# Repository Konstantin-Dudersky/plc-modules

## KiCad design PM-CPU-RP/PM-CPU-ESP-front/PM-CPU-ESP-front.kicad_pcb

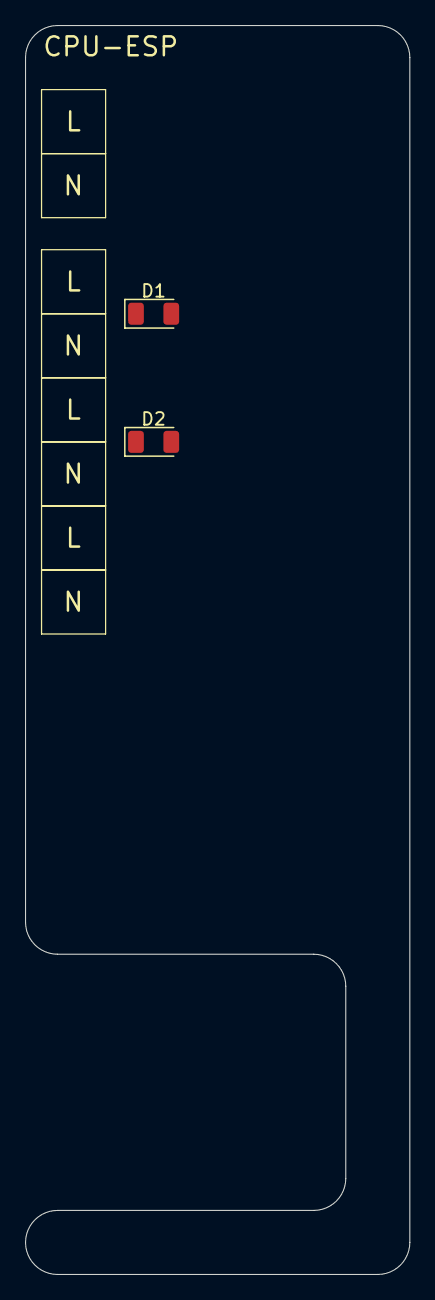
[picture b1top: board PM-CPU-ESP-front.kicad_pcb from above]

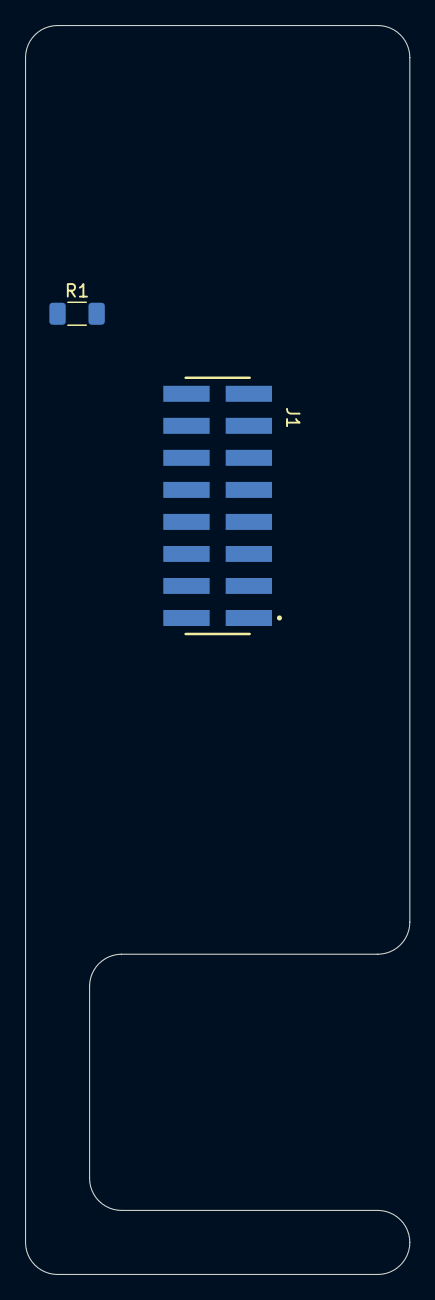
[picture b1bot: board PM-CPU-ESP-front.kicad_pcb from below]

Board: 2 copper layers, 30.5 x 99.1 mm, 4 parts (2 on the bottom side), 3 nets, no tracks yet.

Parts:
D1, D2: KPTD-3216ZGC; LED_KPTD-3216ZGC
J1: Conn_02x08_Odd_Even; Conn_02x08_pin
R1: 270; R_1206_3216Metric_Pad1.30x1.75mm_HandSolder

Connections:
+5V: D2.2 (A), R1.2
GND: D1.1 (K), D2.1 (K)
unnamed: D1.2 (A), R1.1

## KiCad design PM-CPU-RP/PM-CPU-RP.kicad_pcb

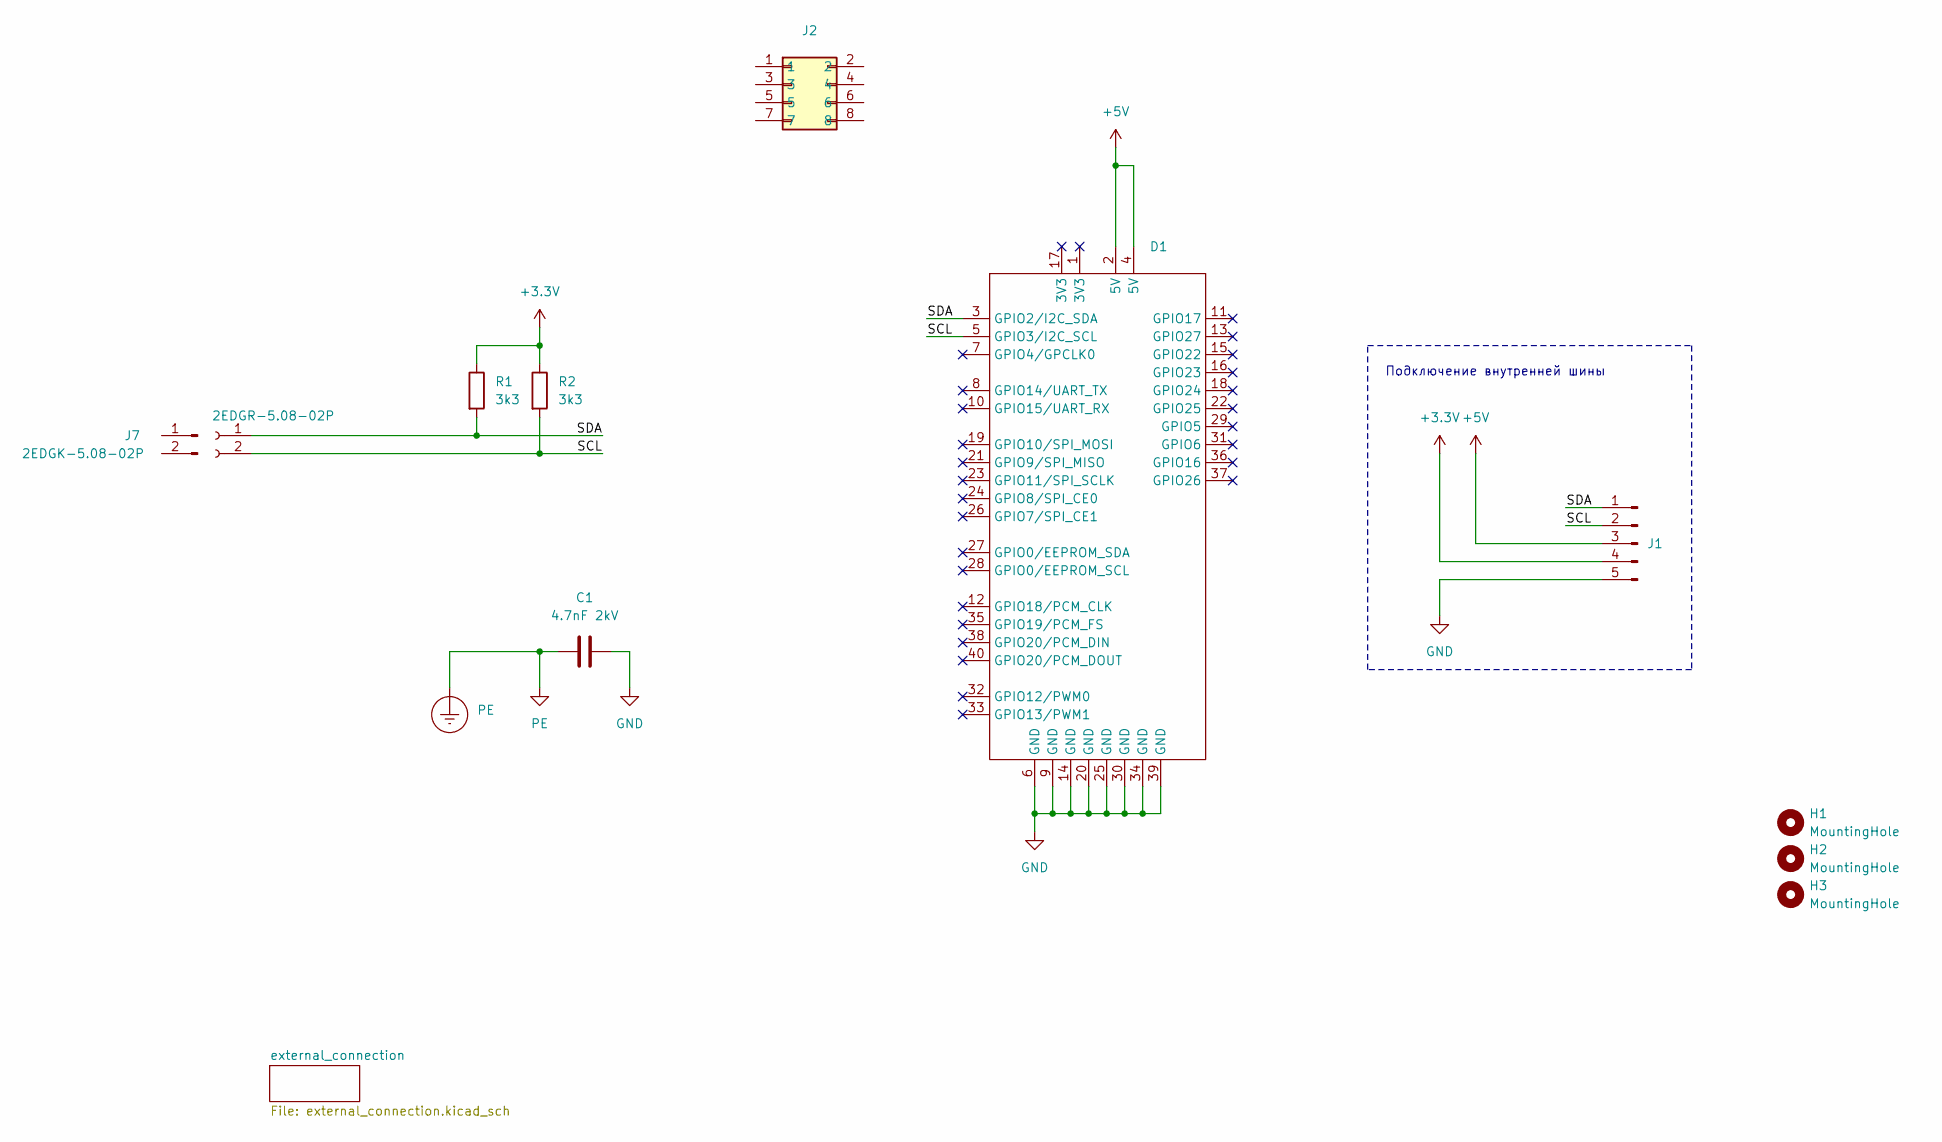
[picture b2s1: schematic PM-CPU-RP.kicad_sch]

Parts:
C1: 4.7nF 2kV; C_1812_4532Metric_Pad1.57x3.40mm_HandSolder; part_ipn C_4.7nF_2kV_1812
D1: RaspberryPi
H1, H2, H3: MountingHole; MountingHole_3.2mm_M3
J1: PinHeader_01x05_P2.54_THT_angle; PinHeader_1x05_P2.54mm_Horizontal; part_ipn PinHeader_01x05_P2.54_THT_angle
J2: PM-front-02x04
J7: 2EDGK-5.08-02P
J8: 2EDGR-5.08-02P; Degson_2EDGR-5.08-02P
PE1: PE
R1, R2: 3k3; R_1206_3216Metric_Pad1.30x1.75mm_HandSolder

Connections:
+3.3V: J1.4, R1.1, R2.1
+5V: D1.2 (5V), D1.4 (5V), J1.3
/SCL: D1.5 (GPIO3/I2C_SCL), J1.2, J8.2, R2.2
/SDA: D1.3 (GPIO2/I2C_SDA), J1.1, J8.1, R1.2
GND: C1.2, D1.6 (GND), D1.9 (GND), D1.14 (GND), D1.20 (GND), D1.25 (GND), D1.30 (GND), D1.34 (GND), D1.39 (GND), J1.5
PE: C1.1, PE1.1

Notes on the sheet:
Подключение внутренней шины

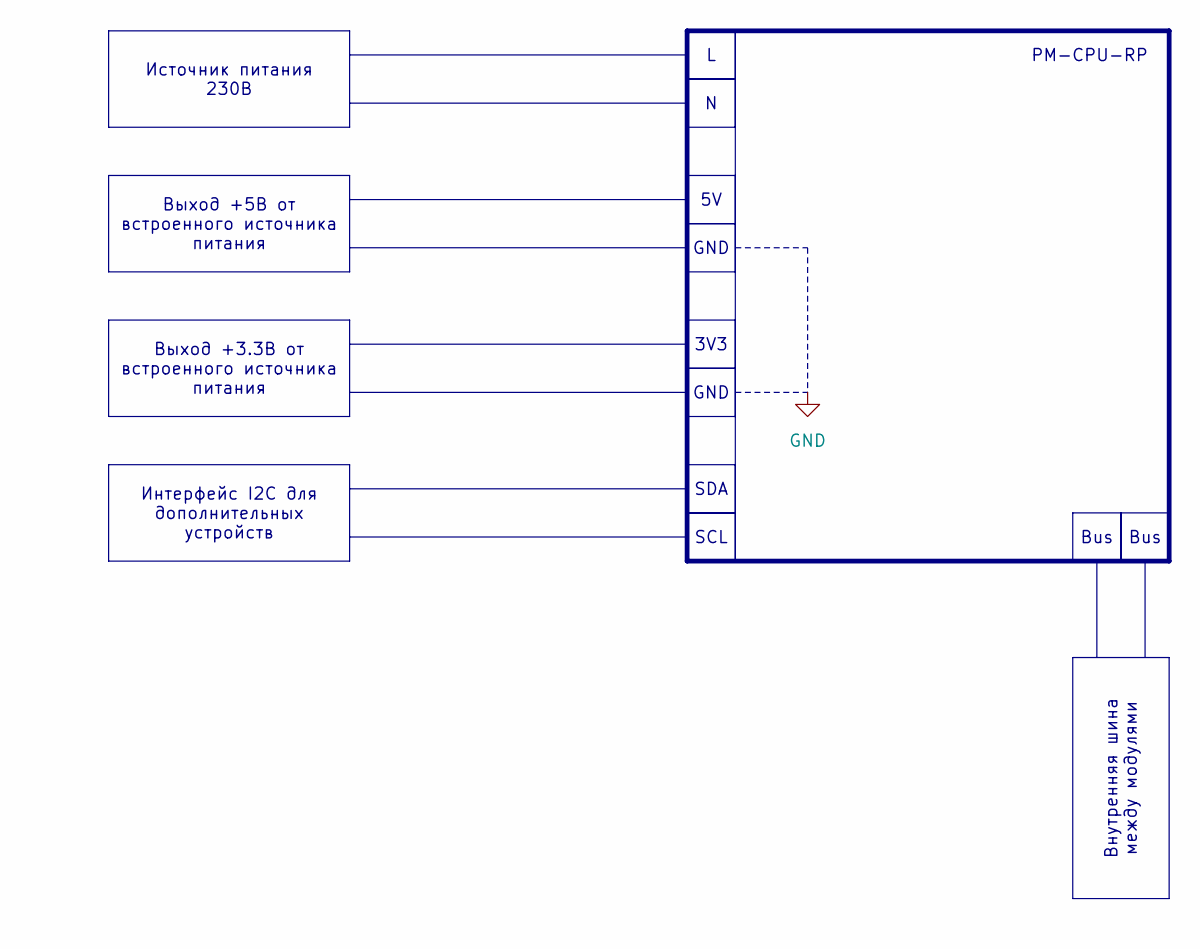
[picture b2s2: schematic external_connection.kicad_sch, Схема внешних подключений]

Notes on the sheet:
Интерфейс I2C для дополнительных устройств
Внутренняя шина между модулями
3V3
Выход +5В от встроенного источника питания
SCL
GND
Bus
Источник питания 230В
SDA
Выход +3.3В от встроенного источника питания
PM-CPU-RP

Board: 2 copper layers, 13 parts (2 on the bottom side), 6 nets, no tracks yet.

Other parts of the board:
kicad_logo: KiCad-Logo2_5mm_SilkScreen
oshw_logo: OSHW-Symbol_6.7x6mm_SilkScreen

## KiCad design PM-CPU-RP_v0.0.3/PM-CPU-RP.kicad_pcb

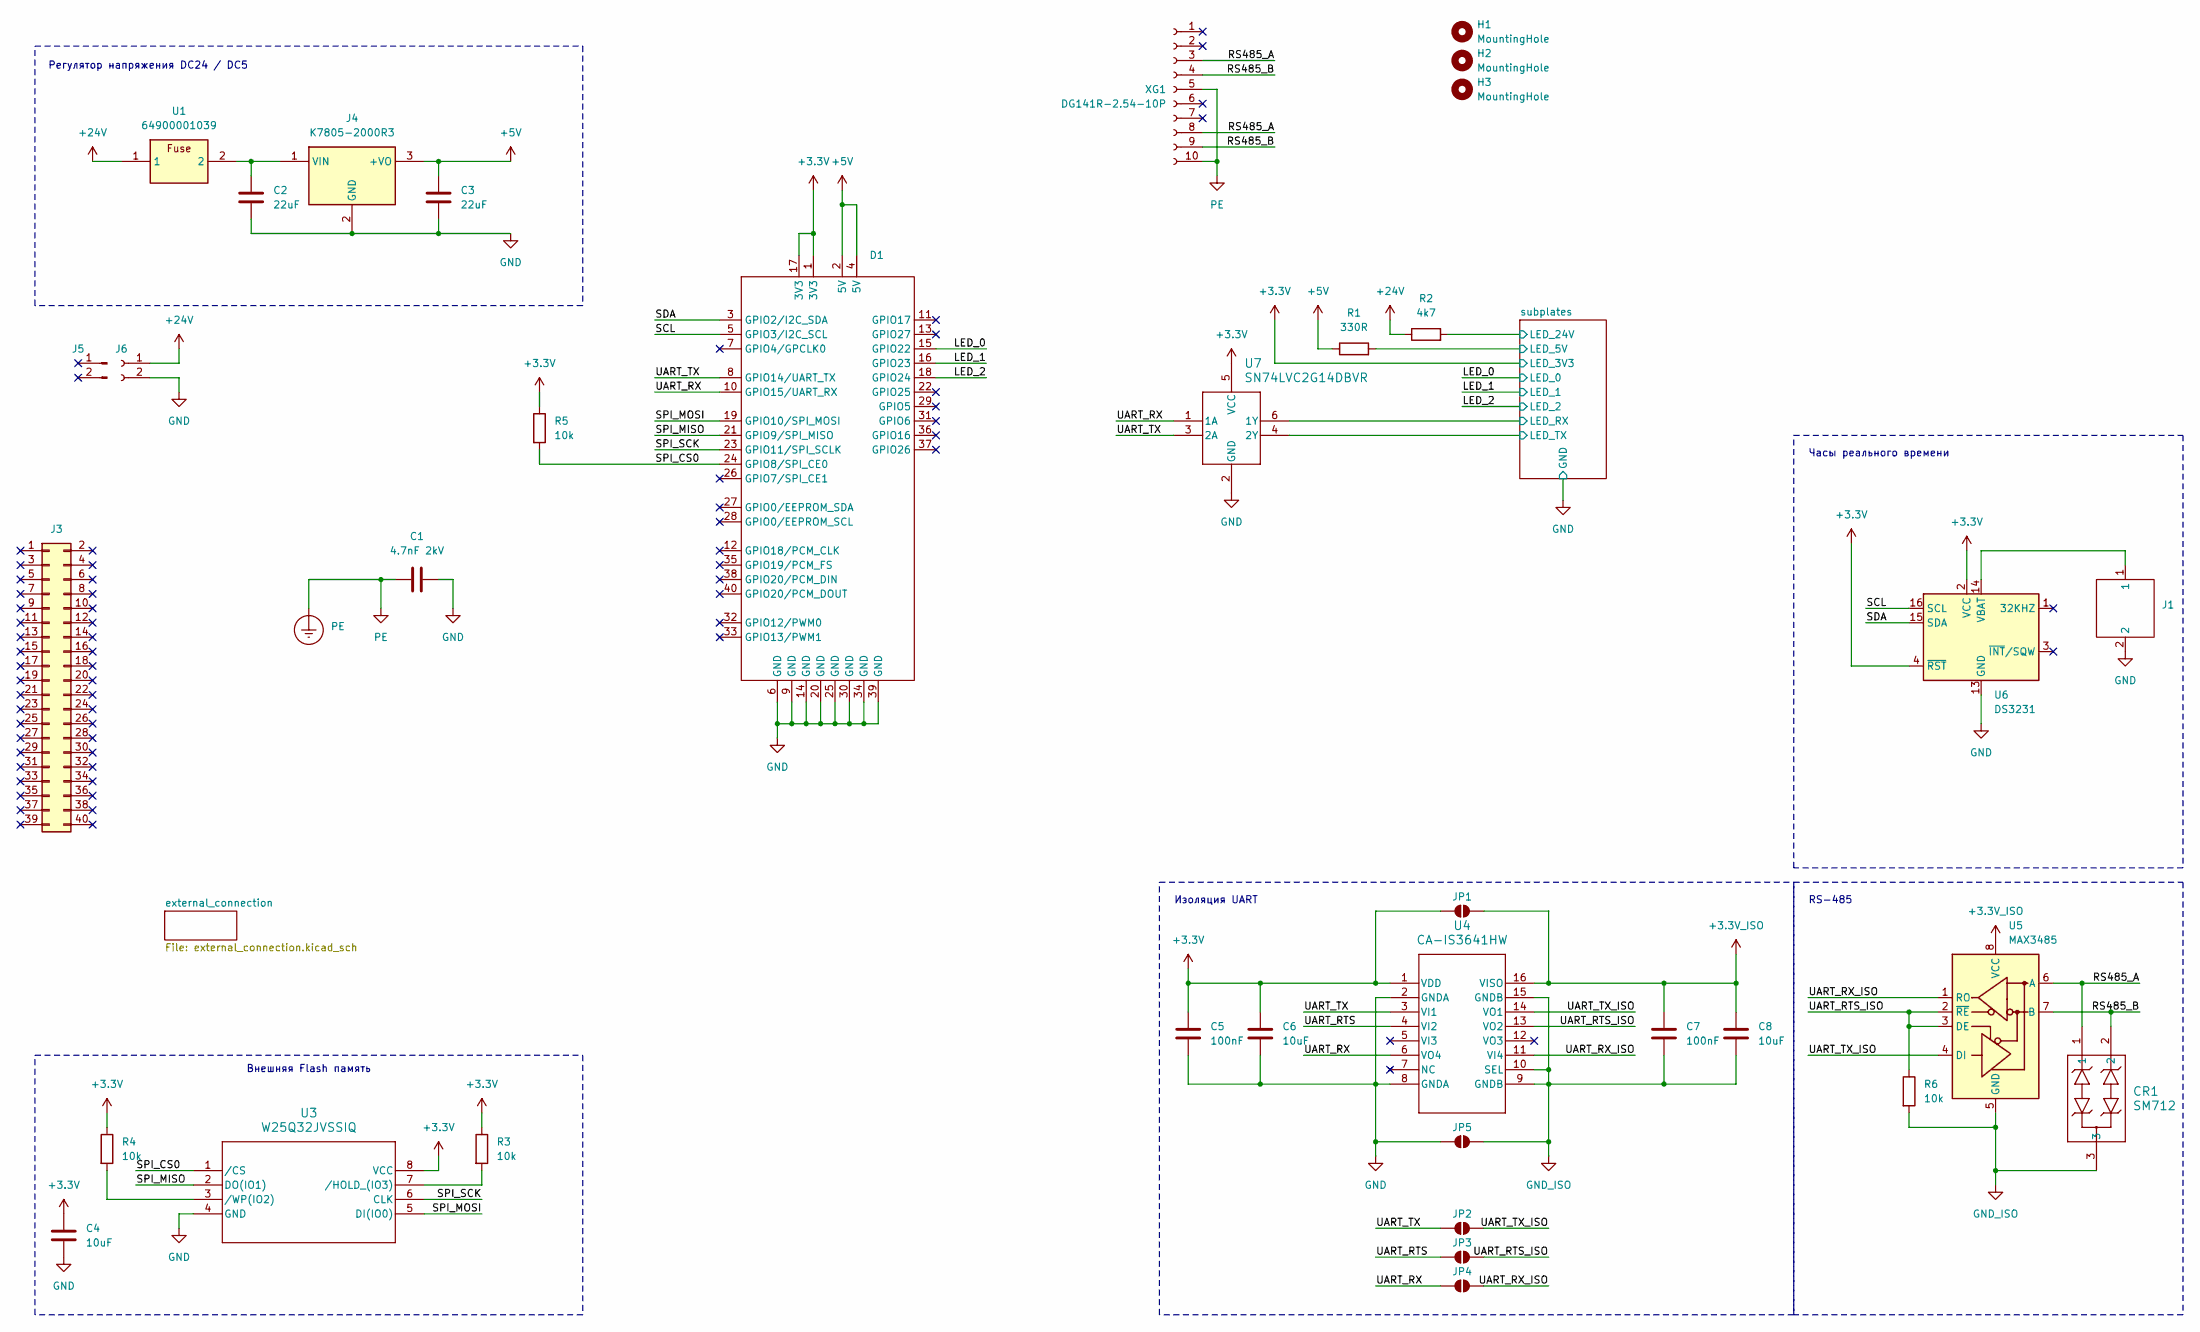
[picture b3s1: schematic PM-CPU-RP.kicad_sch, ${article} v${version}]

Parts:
C1: 4.7nF 2kV; C_1812_4532Metric_Pad1.57x3.40mm_HandSolder; part_ipn C_4.7nF_2kV_1812
C2, C3: 22uF; C_2220_5750Metric_Pad1.97x5.40mm_HandSolder; part_ipn C_22uF_50V_2220
C4, C6, C8: 10uF; C_1206_3216Metric_Pad1.33x1.80mm_HandSolder; part_ipn C_10uF_16V_1206
C5, C7: 100nF; C_1206_3216Metric_Pad1.33x1.80mm_HandSolder; part_ipn C_100nF_50V_1206
CR1: SM712; SOT23-3_LTF
D1: RaspberryPi
H1, H2, H3: MountingHole; MountingHole_3.2mm_M3
J1: BS-12-A1AJ002-F
J3: FemaleHeader_02x20_P2.54_SMD_straight; part_ipn FemaleHeader_02x20_P2.54_SMD_straight
J4: K7805-2000R3; Manufacturer_Part_Number K7805-2000R3
J5: 2EDGK-5.08-02P; part_ipn 2EDGK-5.08-02P
J6: 2EDGR-5.08-02P; Degson_2EDGR-5.08-02P; part_ipn 2EDGR-5.08-02P
JP1, JP2, JP3, JP4, JP5: SolderJumper_2_Open; SolderJumper-2_P1.3mm_Open_RoundedPad1.0x1.5mm
PE1: PE
R1: 330R; R_1206_3216Metric_Pad1.30x1.75mm_HandSolder; part_ipn R_330R_1206_1%
R2: 4k7; R_1206_3216Metric_Pad1.30x1.75mm_HandSolder; part_ipn R_4k7_1206_1%
R3, R4, R5, R6: 10k; R_1206_3216Metric_Pad1.30x1.75mm_HandSolder; part_ipn R_10k_1206_1%
U1: 64900001039; Fuseholder; Manufacturer_Part_Number 64900001039; Mouser Part Number 576-64900001039
U3: W25Q32JVSSIQ; SOIC-8_5P28X5P28_WIN-M
U4: CA-IS3641HW; SOIC16-WBW_CLG-M; part_ipn CA-IS3641HW
U5: MAX3485; SOIC-8_3.9x4.9mm_P1.27mm
U6: DS3231; SOIC-16W_7.5x10.3mm_P1.27mm; part_ipn DS3231SN
U7: SN74LVC2G14DBVR; DBV6-M
XG1: DG141R-2.54-10P; part_ipn DG141R-2.54-10P

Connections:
+3.3V: C4.1, C5.1, C6.1, D1.1 (3V3), D1.17 (3V3), JP1.1 (A), R3.1, R4.1, R5.1, U3.8 (VCC), U4.1 (VDD), U6.2 (VCC), U6.4 (~RST), U7.5 (VCC); also elsewhere on the board
+3.3V_ISO: C7.1, C8.1, JP1.2 (B), U4.16 (VISO), U5.8 (VCC)
+5V: C3.1, D1.2 (5V), D1.4 (5V), J4.3 (+VO), R1.1
+24V: J6.1, R2.1, U1.1
/LED_0: D1.15 (GPIO22); also elsewhere on the board
/LED_1: D1.16 (GPIO23); also elsewhere on the board
/LED_2: D1.18 (GPIO24); also elsewhere on the board
/RS485_A: CR1.1, U5.6 (A), XG1.3, XG1.8
/RS485_B: CR1.2, U5.7 (B), XG1.4, XG1.9
/SCL: D1.5 (GPIO3/I2C_SCL), U6.16 (SCL)
/SDA: D1.3 (GPIO2/I2C_SDA), U6.15 (SDA)
/SPI_CS0: D1.24 (GPIO8/SPI_CE0), R5.2, U3.1 (/CS)
/SPI_MISO: D1.21 (GPIO9/SPI_MISO), U3.2 (DO(IO1))
/SPI_MOSI: D1.19 (GPIO10/SPI_MOSI), U3.5 (DI(IO0))
/SPI_SCK: D1.23 (GPIO11/SPI_SCLK), U3.6 (CLK)
/UART_RTS: JP3.1 (A), U4.4 (VI2)
/UART_RTS_ISO: JP3.2 (B), R6.1, U4.13 (VO2), U5.2 (~RE), U5.3 (DE)
/UART_RX: D1.10 (GPIO15/UART_RX), JP4.1 (A), U4.6 (VO4), U7.1 (1A)
/UART_RX_ISO: JP4.2 (B), U4.11 (VI4), U5.1 (RO)
/UART_TX: D1.8 (GPIO14/UART_TX), JP2.1 (A), U4.3 (VI1), U7.3 (2A)
/UART_TX_ISO: JP2.2 (B), U4.14 (VO1), U5.4 (DI)
/subplates/LED_5V: R1.2; also elsewhere on the board
/subplates/LED_24V: R2.2; also elsewhere on the board
/subplates/LED_RX: U7.6 (1Y); also elsewhere on the board
/subplates/LED_TX: U7.4 (2Y); also elsewhere on the board
GND: C1.2, C2.2, C3.2, C4.2, C5.2, C6.2, D1.6 (GND), D1.9 (GND), D1.14 (GND), D1.20 (GND), D1.25 (GND), D1.30 (GND), D1.34 (GND), D1.39 (GND), J1.2, J4.2 (GND), J6.2, JP5.1 (A), U3.4 (GND), U4.2 (GNDA), U4.8 (GNDA), U6.5 (GND), U6.6 (GND), U6.7 (GND), U6.8 (GND), U6.9 (GND), U6.10 (GND), U6.11 (GND), U6.12 (GND), U6.13 (GND), U7.2 (GND); also elsewhere on the board
GND_ISO: C7.2, C8.2, CR1.3, JP5.2 (B), R6.2, U4.9 (GNDB), U4.10 (SEL), U4.15 (GNDB), U5.5 (GND)
unnamed: C2.1, J4.1 (VIN), U1.2
unnamed: R3.2, U3.7 (/HOLD_(IO3))
unnamed: R4.2, U3.3 (/WP(IO2))
unnamed: J1.1, U6.14 (VBAT)
PE: C1.1, PE1.1, XG1.5, XG1.10

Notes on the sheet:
Изоляция UART
RS-485
Внешняя Flash память
Часы реального времени
Регулятор напряжения DC24 / DC5

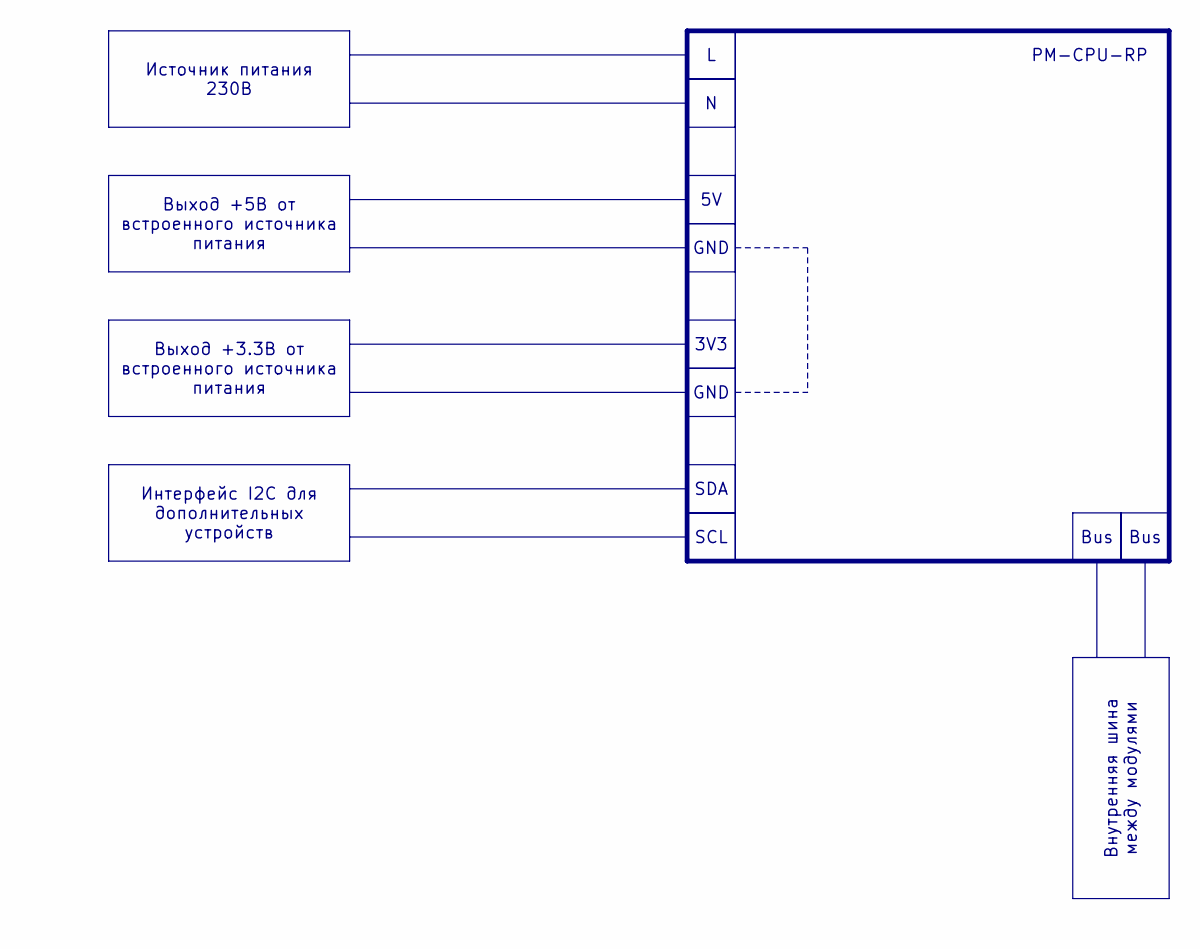
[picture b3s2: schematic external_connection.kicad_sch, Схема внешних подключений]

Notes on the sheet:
Интерфейс I2C для дополнительных устройств
Внутренняя шина между модулями
3V3
Выход +5В от встроенного источника питания
SCL
GND
Bus
Источник питания 230В
SDA
Выход +3.3В от встроенного источника питания
PM-CPU-RP

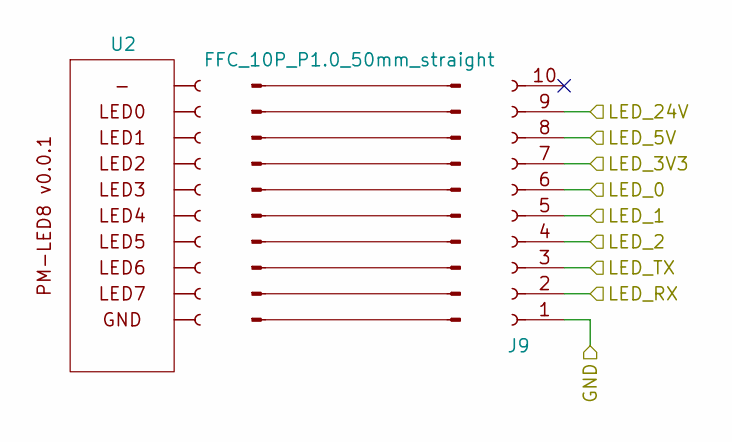
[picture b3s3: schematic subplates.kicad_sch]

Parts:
J8: FFC_10P_P1.0_50mm_straight; part_ipn FFC_10P_P1.0_50mm_reverse
J9: AFA07-S10FCC-00; CONN10_AFA07-S10_JUS
U2: PM-LED8_v0.0.1; PM-LED_v0.0.1

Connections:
+3.3V: J9.7; also elsewhere on the board
/LED_0: J9.6; also elsewhere on the board
/LED_1: J9.5; also elsewhere on the board
/LED_2: J9.4; also elsewhere on the board
/subplates/LED_5V: J9.8; also elsewhere on the board
/subplates/LED_24V: J9.9; also elsewhere on the board
/subplates/LED_RX: J9.2; also elsewhere on the board
/subplates/LED_TX: J9.3; also elsewhere on the board
GND: J9.1; also elsewhere on the board

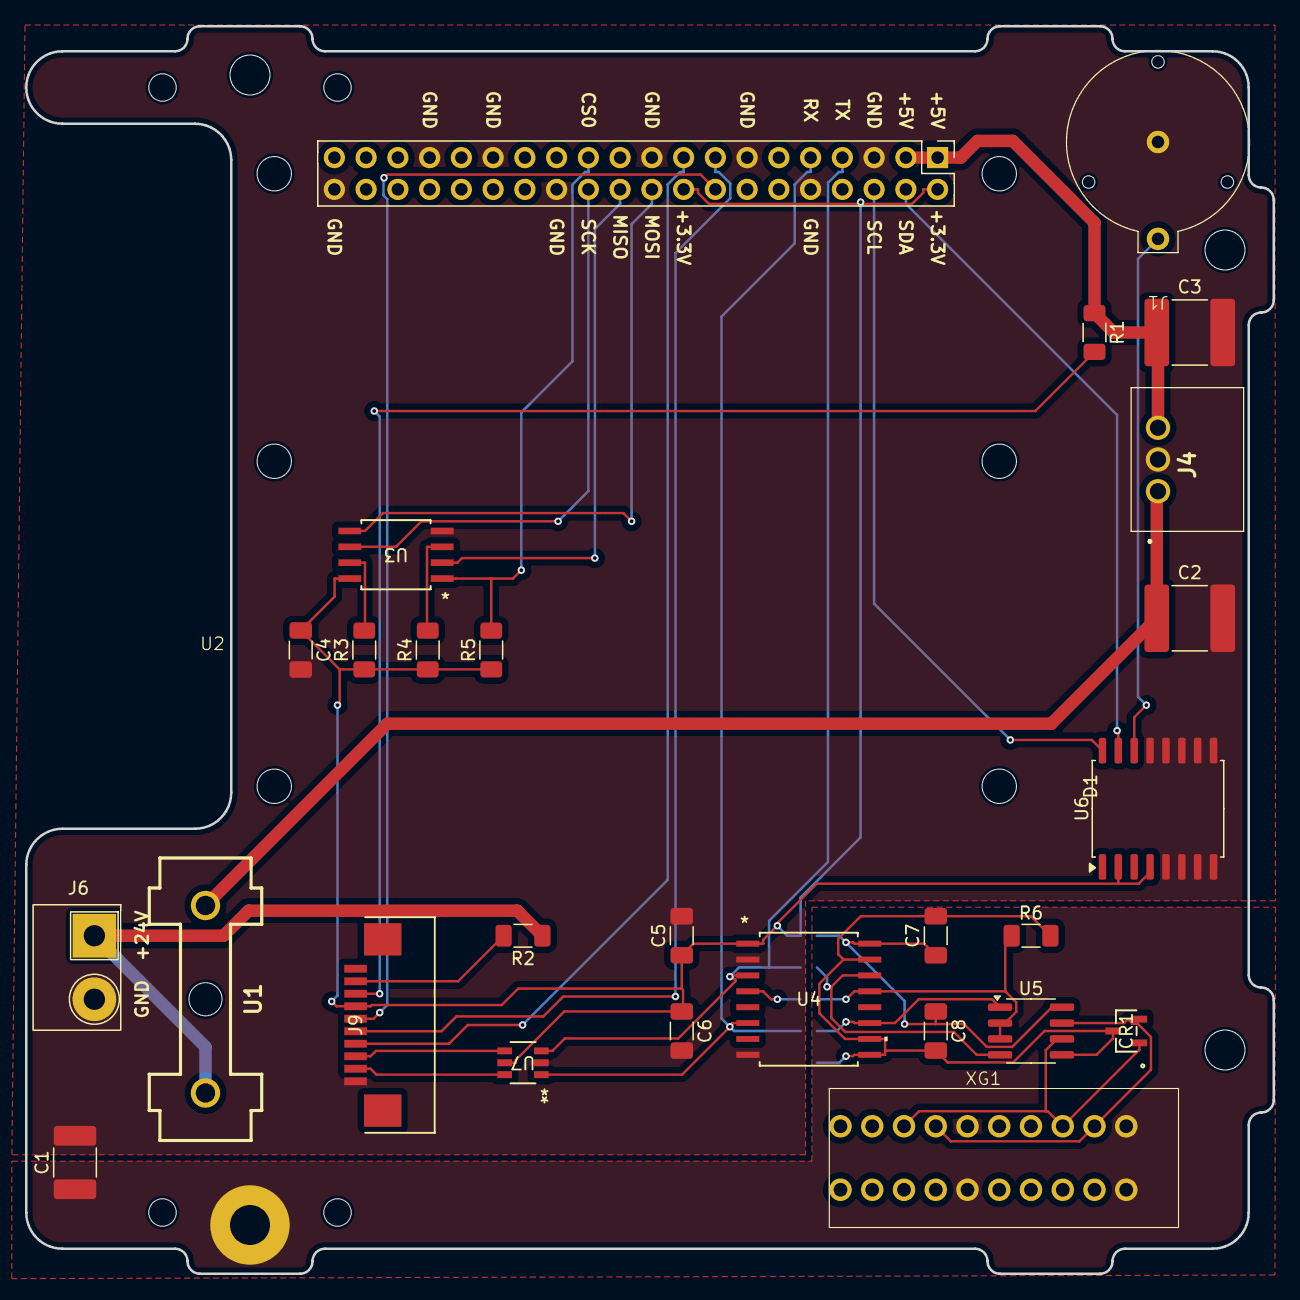
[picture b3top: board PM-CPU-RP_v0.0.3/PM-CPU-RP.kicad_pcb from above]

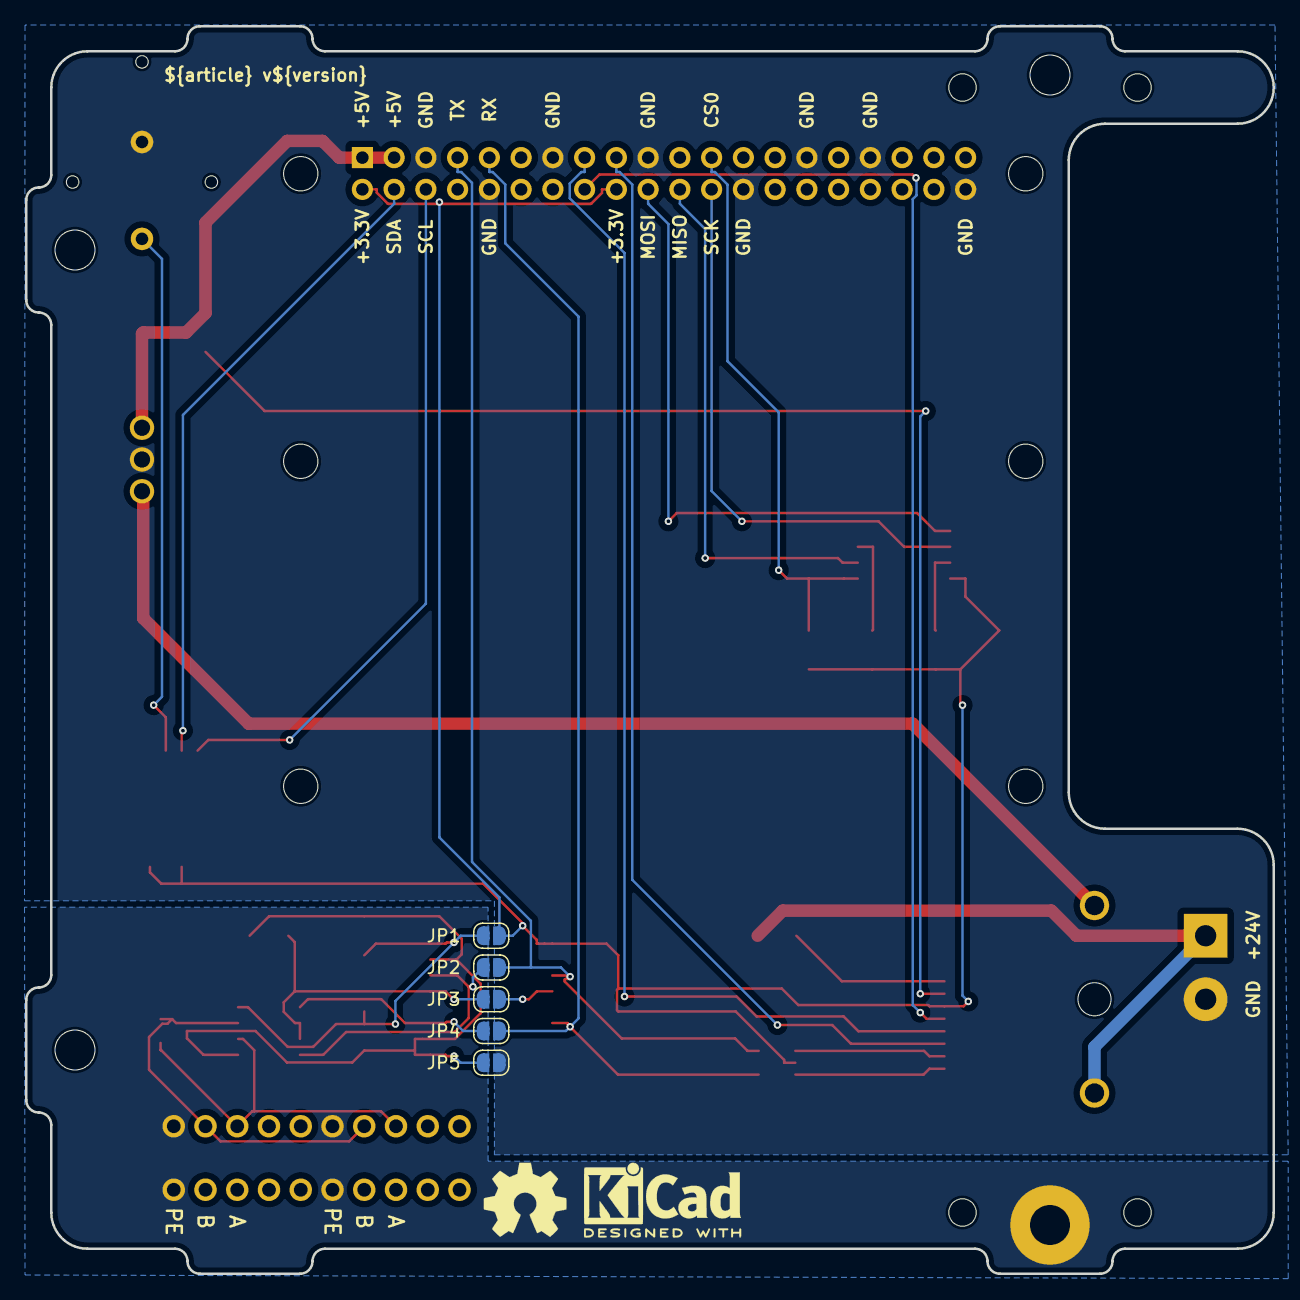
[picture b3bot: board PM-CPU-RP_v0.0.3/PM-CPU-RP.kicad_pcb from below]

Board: 2 copper layers, 99.8 x 99.8 mm, 39 parts (7 on the bottom side), 32 nets.

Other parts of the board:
kicad_logo: KiCad-Logo2_5mm_SilkScreen
oshw_logo: OSHW-Symbol_6.7x6mm_SilkScreen

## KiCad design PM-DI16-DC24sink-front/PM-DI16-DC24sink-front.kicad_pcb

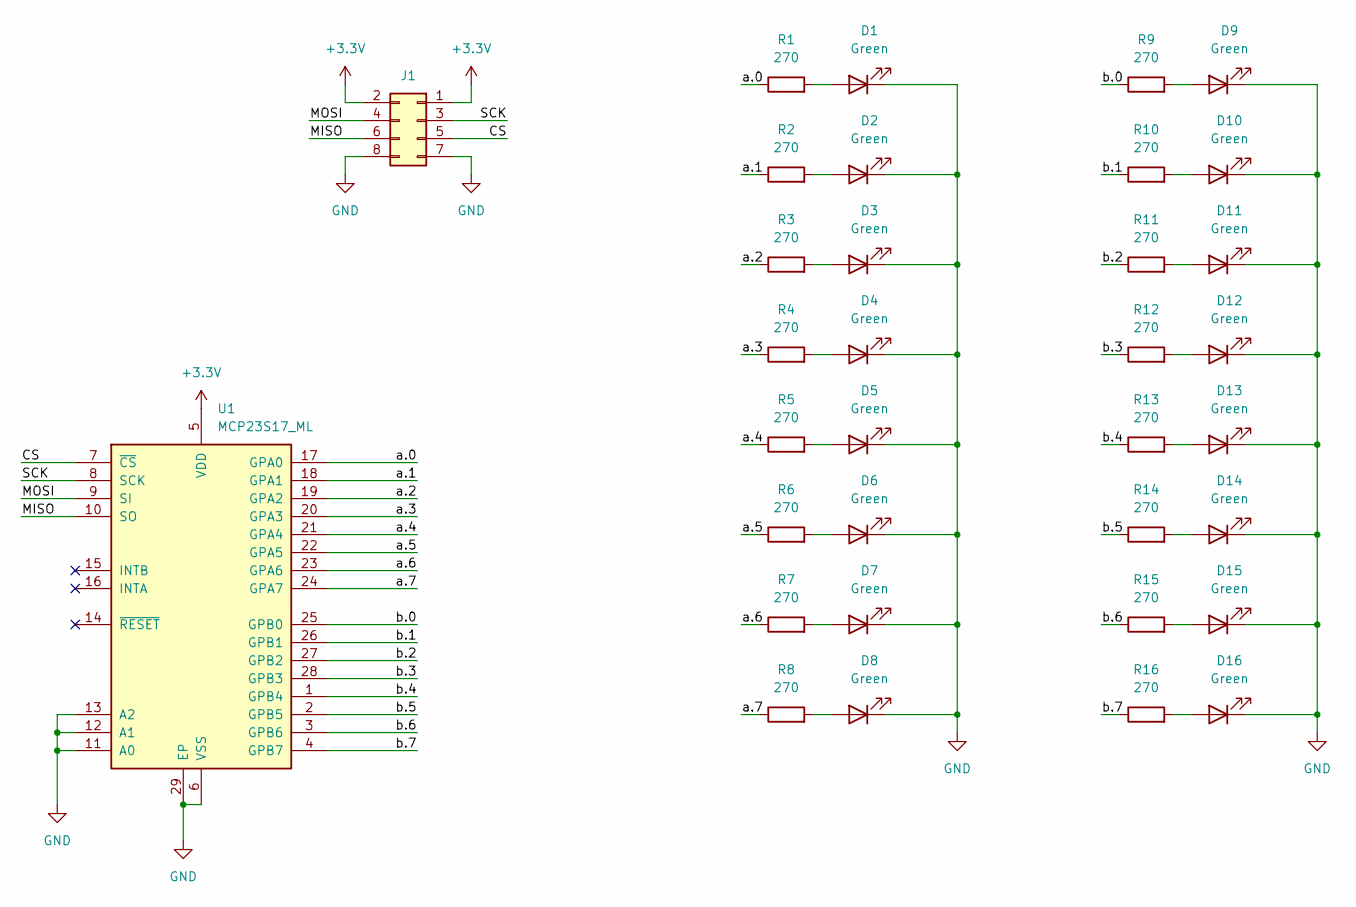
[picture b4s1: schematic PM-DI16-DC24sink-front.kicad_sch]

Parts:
D1, D2, D3, D4, D5, D6, D7, D8, D9, D10, D11, D12, D13, D14, D15, D16: Green; LED_1206_3216Metric_ReverseMount_Hole1.8x2.4mm; part_ipn LED_green_1206_reverse
J1: PinHeader_02x04_P2.54_THT_angle; PinHeader_2x04_P2.54mm_Horizontal; part_ipn PinHeader_02x04_P2.54_THT_angle
R1, R2, R3, R4, R5, R6, R7, R8, R9, R10, R11, R12, R13, R14, R15, R16: 270; R_1206_3216Metric_Pad1.30x1.75mm_HandSolder; part_ipn R_270_1206_1%
U1: MCP23S17_ML; QFN-28-1EP_6x6mm_P0.65mm_EP4.25x4.25mm; part_ipn MCP23S17-E/ML

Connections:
+3.3V: J1.1, J1.2, U1.5 (VDD)
/CS: J1.5, U1.7 (~CS)
/MISO: J1.6, U1.10 (SO)
/MOSI: J1.4, U1.9 (SI)
/SCK: J1.3, U1.8 (SCK)
/a.0: R1.1, U1.17 (GPA0)
/a.1: R2.1, U1.18 (GPA1)
/a.2: R3.1, U1.19 (GPA2)
/a.3: R4.1, U1.20 (GPA3)
/a.4: R5.1, U1.21 (GPA4)
/a.5: R6.1, U1.22 (GPA5)
/a.6: R7.1, U1.23 (GPA6)
/a.7: R8.1, U1.24 (GPA7)
/b.0: R9.1, U1.25 (GPB0)
/b.1: R10.1, U1.26 (GPB1)
/b.2: R11.1, U1.27 (GPB2)
/b.3: R12.1, U1.28 (GPB3)
/b.4: R13.1, U1.1 (GPB4)
/b.5: R14.1, U1.2 (GPB5)
/b.6: R15.1, U1.3 (GPB6)
/b.7: R16.1, U1.4 (GPB7)
GND: D1.1 (K), D2.1 (K), D3.1 (K), D4.1 (K), D5.1 (K), D6.1 (K), D7.1 (K), D8.1 (K), D9.1 (K), D10.1 (K), D11.1 (K), D12.1 (K), D13.1 (K), D14.1 (K), D15.1 (K), D16.1 (K), J1.7, J1.8, U1.6 (VSS), U1.11 (A0), U1.12 (A1), U1.13 (A2), U1.29 (EP)
unnamed: D1.2 (A), R1.2
unnamed: D2.2 (A), R2.2
unnamed: D3.2 (A), R3.2
unnamed: D4.2 (A), R4.2
unnamed: D5.2 (A), R5.2
unnamed: D6.2 (A), R6.2
unnamed: D7.2 (A), R7.2
unnamed: D8.2 (A), R8.2
unnamed: D9.2 (A), R9.2
unnamed: D10.2 (A), R10.2
unnamed: D11.2 (A), R11.2
unnamed: D12.2 (A), R12.2
unnamed: D13.2 (A), R13.2
unnamed: D14.2 (A), R14.2
unnamed: D15.2 (A), R15.2
unnamed: D16.2 (A), R16.2

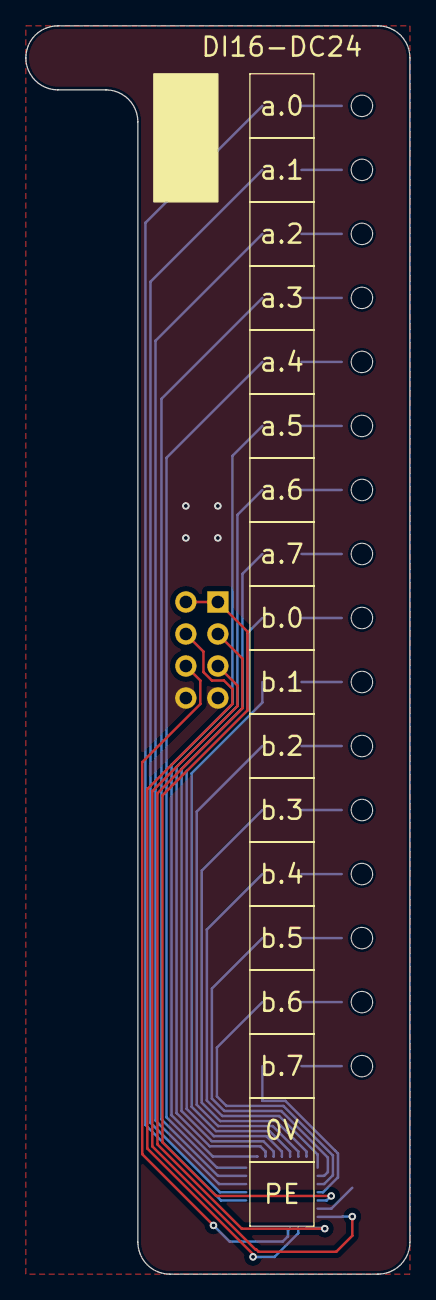
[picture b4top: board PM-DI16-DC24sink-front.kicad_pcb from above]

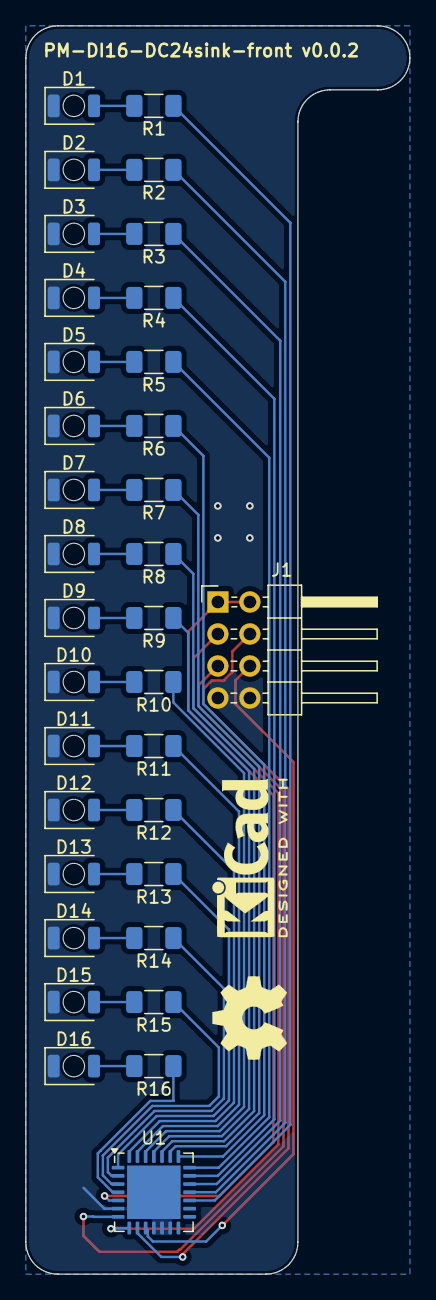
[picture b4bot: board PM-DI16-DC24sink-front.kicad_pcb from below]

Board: 2 copper layers, 30.5 x 99.1 mm, 35 parts (35 on the bottom side), 38 nets.

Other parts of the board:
Logo_kicad: KiCad-Logo2_5mm_SilkScreen
